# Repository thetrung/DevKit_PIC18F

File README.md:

DevKit PIC18F/USB-B
=====================
Basic USB Type-B DevKit I made to learn about PIC18F45XX microcontroller.

**It was initially for USB Type-C, but seem like I was wrong about how popular it actually is in my local stores, so change of plan : switching back to USB Type-B from Rev.2 for ease of self-soldering the boards. But very funny, on Rev.2, while changing the USB-Port, I realize how everything seem to be a little bit closer to what I think it should be. There were a short-circuit (for the 2nd-time) that I didn't realize right inside the USB-port.**

### 1. Basic functionality :
- USB-powered 5V supply.
- USB-HID controllable with PIC18F45k50 with D+/D- pins.
- Reset Button -> Trigger MLCR-pin pull-down -> GND.
- Programming/Debugging with PICKIT-3 via ICSP pins.
- 5 pluggable PORTS : RA, RB, RC, RD, RE.

### 2. TODO / Future extensions :
- Add Array : 
    - 4x4 12mm-Buttons pad.
    - 4x4 LEDs grid.
    - 16 Relays
      
- Add Gyro sensor.
- Add distance sensor.
- Add 12V Booster support.
- Add built-in UART w/ CH340.
- Add LCD2004 support, with/without I2C module.
- Add WIFI/LoRA/Bluetooth by ESP32 support (?).

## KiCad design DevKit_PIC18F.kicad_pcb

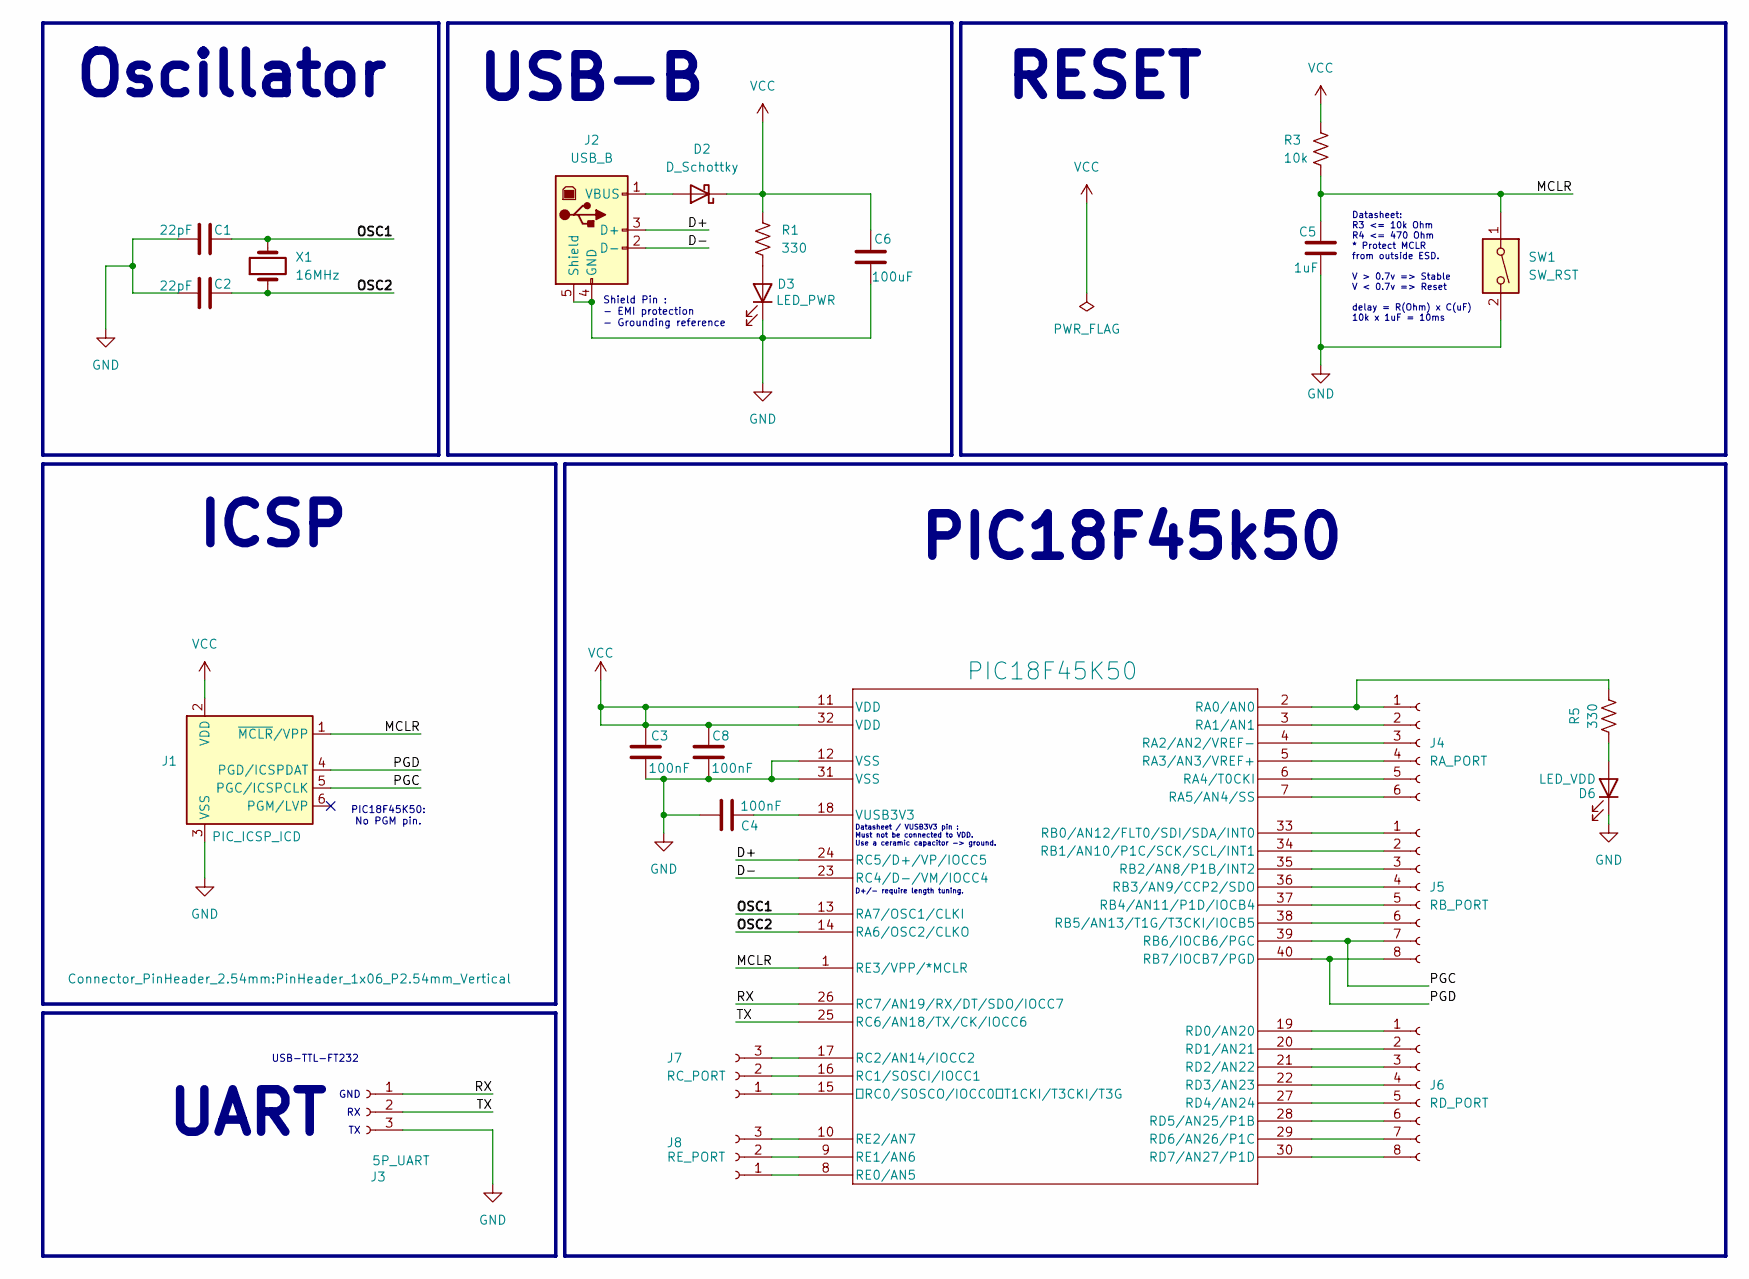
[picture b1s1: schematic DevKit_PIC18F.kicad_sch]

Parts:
C1, C2: 22pF; C_Disc_D3.0mm_W1.6mm_P2.50mm
C3, C8: 100nF; CP_Radial_D4.0mm_P2.00mm
C4: 100nF; C_Disc_D3.0mm_W1.6mm_P2.50mm
C5: 1uF; C_Disc_D3.0mm_W1.6mm_P2.50mm
C6: 100uF; C_Disc_D3.0mm_W1.6mm_P2.50mm
D2: D_Schottky; D_DO-34_SOD68_P7.62mm_Horizontal
D3: LED_PWR; LED_D3.0mm_FlatTop
D6: LED_VDD; LED_D3.0mm_FlatTop
J1: PIC_ICSP_ICD; PinHeader_1x06_P2.54mm_Vertical
J2: USB_B; USB_B_Lumberg_2411_02_Horizontal
J3: 5P_UART; PinSocket_1x03_P2.54mm_Vertical
J4: RA_PORT; PinSocket_1x06_P2.54mm_Vertical
J5: RB_PORT; PinSocket_1x08_P2.54mm_Vertical
J6: RD_PORT; PinSocket_1x08_P2.54mm_Vertical
J7: RC_PORT; PinSocket_1x03_P2.54mm_Vertical
J8: RE_PORT; PinSocket_1x03_P2.54mm_Vertical
PIC18F45K50: PIC18F45K50-I/P; DIP-40_W15.24mm_Socket_LongPads
R1, R5: 330; R_Axial_DIN0204_L3.6mm_D1.6mm_P5.08mm_Horizontal
R3: 10k; R_Axial_DIN0204_L3.6mm_D1.6mm_P5.08mm_Horizontal
SW1: SW_RST; SW_PUSH_6mm
X1: 16MHz; Crystal_HC49-4H_Vertical

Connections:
/D+: J2.3 (D+), PIC18F45K50.24 (RC5/D+/VP/IOCC5)
/D-: J2.2 (D-), PIC18F45K50.23 (RC4/D-/VM/IOCC4)
/MCLR: C5.2, J1.1 (~MCLR/VPP), PIC18F45K50.1 (RE3/VPP/*MCLR), R3.2, SW1.1; also elsewhere on the board
/OSC1: C1.1, PIC18F45K50.13 (RA7/OSC1/CLKI), X1.2
/OSC2: C2.1, PIC18F45K50.14 (RA6/OSC2/CLKO), X1.1
/PGC: J1.5 (PGC/ICSPCLK), J5.7, PIC18F45K50.39 (RB6/IOCB6/PGC)
/PGD: J1.4 (PGD/ICSPDAT), J5.8, PIC18F45K50.40 (RB7/IOCB7/PGD)
/RX: J3.1, PIC18F45K50.26 (RC7/AN19/RX/DT/SDO/IOCC7)
/TX: J3.2, PIC18F45K50.25 (RC6/AN18/TX/CK/IOCC6)
GND: C1.2, C2.2, C3.2, C4.1, C5.1, C6.1, C8.2, D3.1 (K), D6.1 (K), J1.3 (VSS), J2.4 (GND), J2.5 (Shield), J3.3, PIC18F45K50.12 (VSS), PIC18F45K50.31 (VSS), SW1.2
unnamed: D2.2 (A), J2.1 (VBUS)
unnamed: D3.2 (A), R1.2
unnamed: D6.2 (A), R5.1
unnamed: J4.1, PIC18F45K50.2 (RA0/AN0), R5.2
unnamed: J4.2, PIC18F45K50.3 (RA1/AN1)
unnamed: J4.3, PIC18F45K50.4 (RA2/AN2/VREF-)
unnamed: J4.4, PIC18F45K50.5 (RA3/AN3/VREF+)
unnamed 19: J4.5, PIC18F45K50.6 (RA4/T0CKI); also elsewhere on the board
unnamed: J4.6, PIC18F45K50.7 (RA5/AN4/SS)
unnamed: J5.1, PIC18F45K50.33 (RB0/AN12/FLT0/SDI/SDA/INT0)
unnamed: J5.2, PIC18F45K50.34 (RB1/AN10/P1C/SCK/SCL/INT1)
unnamed: J5.3, PIC18F45K50.35 (RB2/AN8/P1B/INT2)
unnamed: J5.4, PIC18F45K50.36 (RB3/AN9/CCP2/SDO)
unnamed: J5.5, PIC18F45K50.37 (RB4/AN11/P1D/IOCB4)
unnamed: J5.6, PIC18F45K50.38 (RB5/AN13/T1G/T3CKI/IOCB5)
unnamed: J6.1, PIC18F45K50.19 (RD0/AN20)
unnamed: J6.2, PIC18F45K50.20 (RD1/AN21)
unnamed: J6.3, PIC18F45K50.21 (RD2/AN22)
unnamed: J6.4, PIC18F45K50.22 (RD3/AN23)
unnamed: J6.5, PIC18F45K50.27 (RD4/AN24)
unnamed: J6.6, PIC18F45K50.28 (RD5/AN25/P1B)
unnamed: J6.7, PIC18F45K50.29 (RD6/AN26/P1C)
unnamed: J6.8, PIC18F45K50.30 (RD7/AN27/P1D)
unnamed: J7.1, PIC18F45K50.15 (RC0/SOSCO/IOCC0 T1CKI/T3CKI/T3G)
unnamed: J7.2, PIC18F45K50.16 (RC1/SOSCI/IOCC1)
unnamed: J7.3, PIC18F45K50.17 (RC2/AN14/IOCC2)
unnamed: J8.1, PIC18F45K50.8 (RE0/AN5)
unnamed: J8.2, PIC18F45K50.9 (RE1/AN6)
unnamed: J8.3, PIC18F45K50.10 (RE2/AN7)
unnamed: C4.2, PIC18F45K50.18 (VUSB3V3)
VCC: C3.1, C6.2, C8.1, D2.1 (K), J1.2 (VDD), PIC18F45K50.11 (VDD), PIC18F45K50.32 (VDD), R1.1, R3.1; also elsewhere on the board

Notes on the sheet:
RESET
USB-B
D+/- require length tuning.
ICSP
Shield Pin : - EMI protection - Grounding reference
Datasheet / VUSB3V3 pin : Must not be connected to VDD. Use a ceramic capacitor -> ground.
GND
UART
Datasheet: R3 <= 10k Ohm R4 <= 470 Ohm * Protect MCLR from outside ESD. V > 0.7v => Stable V < 0.7v => Reset delay = R(Ohm) x C(uF) 10k x 1uF = 10ms
USB-TTL-FT232
Oscillator
PIC18F45K50: No PGM pin.
PIC18F45k50

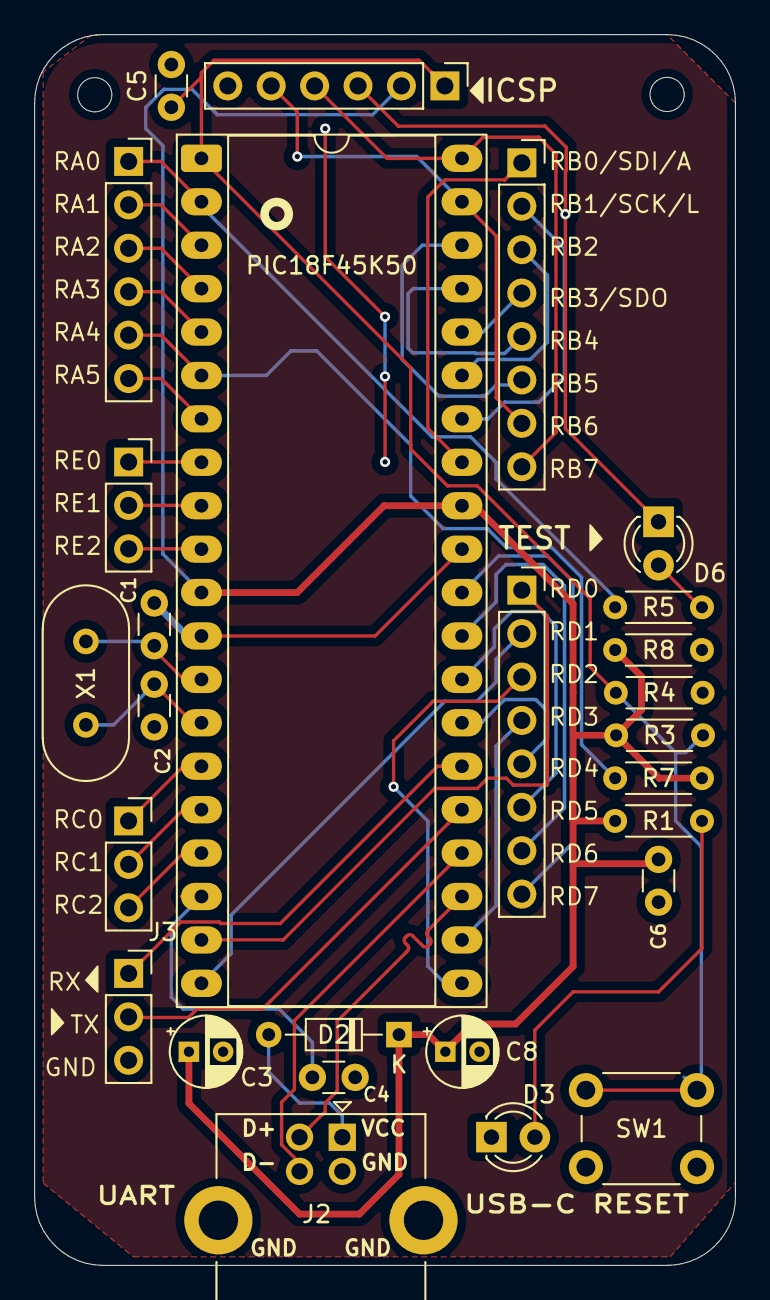
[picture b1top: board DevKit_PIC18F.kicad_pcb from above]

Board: 2 copper layers, 41.0 x 72.0 mm, 27 parts (0 on the bottom side), 41 nets.

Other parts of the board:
R4: 470; R_Axial_DIN0204_L3.6mm_D1.6mm_P5.08mm_Horizontal
R7: 10k; R_Axial_DIN0204_L3.6mm_D1.6mm_P5.08mm_Horizontal
R8: 330; R_Axial_DIN0204_L3.6mm_D1.6mm_P5.08mm_Horizontal

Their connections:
/MCLR: R4.1; also elsewhere on the board
unnamed 19: R7.2; also elsewhere on the board
VCC: R7.1, R8.1; also elsewhere on the board

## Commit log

2024-09-21 Finished basic schematic for PIC18F45k50 Dev Board.
2024-09-22 Change USB-B -> USB-C & Added EdgeCut.
2024-09-22 Routed & Finished Rev.1
2024-09-22 Overview Image of Rev.1
2024-09-22 Fixed Crystal Error & re-routed some more.
2024-09-22 refine routing
2024-09-23 Added ICSP LED, D+/- tuned length, Cap placement/footprint update.
2024-09-23 Add LED/Diode-S->ICSP.
2024-09-23 refined & ordered to fabricate test pcs.
2024-09-25 Switch USB-C -> USB-B for availability.
2024-09-25 Refine/Fix Short-circuit on USB-B
2024-09-25 Update Images.
2024-09-25 move images -> /Images
2024-09-25 refine schematic.
2025-01-13 Fix Bug : remove bridge as we don't need it.
2025-02-22 update rev -> rev.3 13th Jan, 2025: remove bridge
2025-02-22 Updaet Rev.4 : Flip:ICSP+ Move->LED, +Test_LED->RD0, Group all Resistors.
2025-02-22 Update Images
2025-02-22 Rev.5 : remove redundant LED D1
2025-02-22 merged changes
2025-02-27 rev.6: fixed LED-D6 -> GND instead VCC pull-up style.
2025-02-28 migrate -> KiCAD 9.0.0
2025-03-08 Fix PWR_Flag & GND on PCB
2025-04-02 Update Rev.8: Fix SCH bug, remove D/R/L from ISCP & D6->RA0
